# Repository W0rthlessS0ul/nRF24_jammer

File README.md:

<div align="center">
  
  <h1> 🌟 nRF24 Jammer 🌟 </h1>
</div>

Welcome to the **nRF24 Jammer** repository! 🎉 Dive into the world of RF interference with this unique project based on the ESP32 and nRF24 technology.

## 📚 Table of Contents
- [🚀 What Can You Do with This?](#-what-can-you-do-with-this)
- [📱 Ported Firmware](#-ported-firmware)
- [📟 Supported & Community PCBs](#-supported-&-community-pcbs)
- [📋 List of Components](#-list-of-components)
- [🧑‍🔧 Let's Get Started with Soldering!](#-lets-get-started-with-soldering)
- [🛠️ Build From Source](#-build-from-source)
- [📦 Flash Firmware](#-flash-firmware)
- [🎮 Device Control](#-device-control)
- [🌐 Web Interface](#-Web-Interface)
- [🔌 Serial Interface](#-Serial-Interface)
- [🎉 Final Outcome](#-final-outcome)
- [🙏 Acknowledgments](#-acknowledgments)
- [🤝 Project Supporters](#-project-supporters)
- [❤️ Support the project](#-support-the-project)
- [⭐ Star History](#-star-history)

-----

## 🚀 What Can You Do with This?
This amazing jammer is built on the **ESP32** architecture integrated with **configurable numbers of nRF24** modules. With its extraordinary capabilities, you can effectively disrupt signals across different technologies including:
- **Bluetooth** 🔊
- **BLE** 📱
- **Drones** 🚁
- **Wi-Fi** 📶
- **Zigbee**📡

-----

## 📱 Ported Firmware

| Device       | Repository URL                                                      |
|--------------|---------------------------------------------------------------------|
| Flipper Zero | [FZ_nRF24_jammer](https://github.com/W0rthlessS0ul/FZ_nRF24_jammer) |
| LOLIN32 Lite | [nRF24_jammer](https://github.com/gitati16/nRF24_jammer)            |

-----

## 📋 List of Components
To bring this project to life, you will need the following components:

1. <details><summary><b>nRF24 modules 🛠️</b></summary>

    *Any nRF24 modules are suitable, but **CDEBYTE E01-2G4M27D** is recommended*

   </details>

2. **ESP-WROOM-32** ⚙️
3. **16V capacitors** rated at **100µF** 🔋
4. **128x32 or 128x64 OLED display** 📺 *(optional)*
5. **Tactile button** 🔘 *(optional)*

-----

## 📟 Supported & Community PCBs

| Preview | Author | Rev | Board README |
|---------|--------|-----|--------------|
|  | [@W0rthlessS0ul](https://github.com/W0rthlessS0ul) | `v1.0.0` | [README](/PCB/W0rthlessS0ul/v1.0.0/README.md) |

> 💡 **Want to contribute your own PCB design?**  
> If you feel confident in designing a high-quality PCB, feel free to submit your board via a **Pull Request**!  
> 
> - **Well-engineered and verified designs** will be merged directly into the repository.  
> - If there are any doubts regarding layout quality, routing, or component selection, a thread will be opened in **[Discussions](https://github.com/W0rthlessS0ul/nRF24_jammer/discussions)** so the community can review, discuss, and vote on whether it should be added.

-----

## 🧑‍🔧 Let's Get Started with Soldering!

### Connecting First nRF24 module (**optional**)
| **Pin Name** | **ESP32 GPIO** | **Connection**       |
|--------------|----------------|----------------------|
| VCC          | 3.3V          | (+) capacitor        |
| GND          | GND           | (-) capacitor        |
| CE           | GPIO 16       |                      |
| CSN          | GPIO 15       |                      |
| SCK          | GPIO 14       |                      |
| MOSI         | GPIO 13       |                      |
| MISO         | GPIO 12       |                      |
| IRQ          |                |                      |

### Connecting Second nRF24 module (**optional**)
| **Pin Name** | **ESP32 GPIO** | **Connection**       |
|--------------|----------------|----------------------|
| VCC          | 3.3V          | (+) capacitor        |
| GND          | GND           | (-) capacitor        |
| CE           | GPIO 18       |                      |
| CSN          | GPIO 17       |                      |
| SCK          | GPIO 14       |                      |
| MOSI         | GPIO 13       |                      |
| MISO         | GPIO 12       |                      |
| IRQ          |                |                      |

### Connecting Third nRF24 module (**optional**)
| **Pin Name** | **ESP32 GPIO** | **Connection**       |
|--------------|----------------|----------------------|
| VCC          | 3.3V          | (+) capacitor        |
| GND          | GND           | (-) capacitor        |
| CE           | GPIO 23       |                      |
| CSN          | GPIO 19       |                      |
| SCK          | GPIO 14       |                      |
| MOSI         | GPIO 13       |                      |
| MISO         | GPIO 12       |                      |
| IRQ          |                |                      |

### Connecting Fourth nRF24 module (**optional**)
| **Pin Name** | **ESP32 GPIO** | **Connection**       |
|--------------|----------------|----------------------|
| VCC          | 3.3V          | (+) capacitor        |
| GND          | GND           | (-) capacitor        |
| CE           | GPIO 5        |                      |
| CSN          | GPIO 4        |                      |
| SCK          | GPIO 14       |                      |
| MOSI         | GPIO 13       |                      |
| MISO         | GPIO 12       |                      |
| IRQ          |                |                      |

### Connecting Fifth nRF24 module (**optional**)
| **Pin Name** | **ESP32 GPIO** | **Connection**       |
|--------------|----------------|----------------------|
| VCC          | 3.3V          | (+) capacitor        |
| GND          | GND           | (-) capacitor        |
| CE           | GPIO 33       |                      |
| CSN          | GPIO 32       |                      |
| SCK          | GPIO 14       |                      |
| MOSI         | GPIO 13       |                      |
| MISO         | GPIO 12       |                      |
| IRQ          |                |                      |

### OLED Connection (**optional**)
| **Pin Name** | **ESP32 GPIO** |
|--------------|----------------|
| VCC          | 3.3V          |
| GND          | GND           |
| SCL          | GPIO 22       |
| SDA          | GPIO 21       |

### Button Connection (**optional**)
| **Button Actions** | **ESP32 GPIO** |
|--------------|----------------|
| OK          | GPIO 25       |
| NEXT (Optional)             | GPIO 26       |
| PREVIOUS (Optional)            | GPIO 27       |

###### In all configurations the same SCK, MOSI, and MISO pins are used. This is not a mistake - SPI interfaces can share clock and data lines, while proper operation is ensured by separate control signals (CSN and CE)

-----

## 🛠️ Build From Source

#### `This section is addressed to contributors. If you are a regular user of the project, you can skip it`

1. Install **PlatformIO IDE** extension in **VS Code** 
2. Click the PlatformIO icon → Open → Open Project → select your project folder
3. Wait until all dependencies are installed
4. And now you can choose which project to compile in "PROJECT TASKS" or choose "Build all" to compile all kinds of firmware at once.
5. Output .bin files appear in: ```project_root/bin/[env_name]```

###### ⚠️ Important for source builds: Since v2.5.0, this project uses a modified RF24 library (see /lib).

-----

## 📦 Flash Firmware
<details>
<summary><strong>Manual Update</strong></summary>

<div style="margin-left: 20px;">

Follow these steps to flash the firmware:
1. Download the firmware from the **[releases](https://github.com/W0rthlessS0ul/nRF24_jammer/releases)** section that corresponds to your display
2. Navigate to **ESPWebTool**: [ESPWebTool](https://esp.huhn.me/)
3. Arrange the files as per the table below:

| **Address** | **File Name**                             |
|-------------|-------------------------------------------|
| 0x1000      | bootloader.bin              |
| 0x8000      | partitions.bin              |
| 0x10000     | firmware.bin                          |

4. Click "Flash," and once the installation is complete, **restart your board** and enjoy using your jammer!

</div>
</details>
<details>
<summary><strong>OTA Update</strong></summary>

<div style="margin-left: 20px;">

### This method can only be used if you have firmware version 1.9 or higher installed.
Follow these steps to flash the firmware:
1. Download the firmware from the **[releases](https://github.com/W0rthlessS0ul/nRF24_jammer/releases)** section that corresponds to your display
2. Turn on your device and open a web browser
3. Navigate to the web interface at **192.168.4.1**
4. Click on "**OTA**" and select the file "**firmware.bin**" (`⚠️️ make sure not to choose the bootloader or partitions files`)

</div>
</details>

-----

## 🎮 Device Control 

<details>
<summary><strong>🟢 1-Button Configuration</strong></summary>
<div style="margin-left: 20px;">

#### 📋 Menu Navigation
- **Short press** → Next menu item
- **Long press** → Select menu item

#### 📡 Misc Jammer
- **Short press** → Channel +1
- **Long press** → Continuous channel +1 (every 100ms)
- **Double press** → Select channel

#### 📡 WiFi Attack
- **Short press** → Stop attack
- **Double press** → Switch between jam\deauth

</div>
</details>

<details>
<summary><strong>🔵 2-Button Configuration</strong></summary>
<div style="margin-left: 20px;">

#### 📋 Menu Navigation
- **Next button** short press → Next menu item
- **OK button** short press → Select menu item

#### 📡 Misc Jammer
- **Next button** short press → Channel +1
- **Next button** long press → Continuous channel +1 (every 100ms)
- **OK button** short press → Select channel

#### 📡 WiFi Attack
- **Short press** → Stop attack
- **Next button** → Switch between jam\deauth

</div>
</details>

<details>
<summary><strong>🟣 3-Button Configuration</strong></summary>
<div style="margin-left: 20px;">

#### 📋 Menu Navigation
- **Next button** short press → Next menu item
- **Previous button** short press → Previous menu item
- **OK button** short press → Select menu item

#### 📡 Misc Jammer
- **Next button** short press → Channel +1
- **Next button** long press → Continuous channel +1 (every 100ms)
- **Previous button** short press → Channel -1
- **Previous button** long press → Continuous channel -1 (every 100ms)
- **OK button** short press → Select channel

#### 📡 WiFi Attack
- **Short press** → Stop attack
- **Next button** → Switch between jam\deauth
- **Previous button** → Switch between jam\deauth

</div>
</details>

-----

## 🌐 Web Interface

- To utilize the web interface, please follow the steps outlined below
1. activate the **nRF24 jammer**
2. Connect to the Wi-Fi network named `jammer` using the password `W0rthlessS0ul`
3. open your web browser and navigate to the IP address `192.168.4.1`
4. Now you can control your nRF24 jammer through an web interface

-----

## 🔌 Serial Interface

- To utilize the serial interface, please follow the steps outlined below
1. Activate the **nRF24 jammer**
2. Connect the device to a PC or phone via USB
3. You can use any serial terminals for control, for example: [spacehuhn terminal](https://terminal.spacehuhn.com/)
4. Now write **help** to get a list of commands

-----

## 🎉 Final Outcome

### Normal Spectrum

### Bluetooth Jam Spectrum

### Drone Jam Spectrum

### Wi-Fi Jam Spectrum

### BLE Jam Spectrum

### Zigbee Jam Spectrum

### Misc Jam Spectrum

-----

## 🙏 Acknowledgments
- [smoochiee](https://github.com/smoochiee) - **for the main logic of the jammer.**
- [samukas81](https://github.com/samukas81) - **for suggesting ideas.**

-----

## 🤝 Project Supporters

| **Supporter**                                  | **Contribution**|
|------------------------------------------------|-----------------|
|  [@sergey2735](https://github.com/sergey2735)  |    40.7 ADA     |

-----

## ❤️ Support the Project

If you find this project useful and want to support its ongoing development, consider starring the repository ⭐, following the author, or buying a cup of coffee to keep things fueled! ☕

<div align="center">
  <table width="70%">
    <tr>
      <td width="50%" align="center">
        
      </td>
      <td width="50%" align="center">
        
      </td>
    </tr>
  </table>
</div>

<br>

<details>
<summary><b>🪙 Direct Cryptocurrency Transfer</b></summary>
<br>

| Coin / Network | Direct Wallet Address |
| :--- | :--- |
| 🟧 **Bitcoin (BTC)** | `bc1qvul4mlxxw5h2hnt8knnxdrxuwgpf4styyk20tm` |
| 🔷 **Ethereum (ETH)** | `0x5c54eAb2acFE1c6C866FB4b050d8B69CfB1138Af` |
| ⚪ **Litecoin (LTC)** | `LbdzCsYbxuD341raar6Cg1yKavaDq7fjuV` |
| ⚫ **Ripple (XRP)** | `rKLLPzoBGfqY3pAQPwTFPRYaWjpHSwHNDw` |
| 🔵 **Cardano (ADA)** | `addr1qyz2aku0ucmxqnl60lza23lkx2xha8zmxz9wqxnrtvpjysgy4mdcle3kvp8l5l7964rlvv5d06w9kvy2uqdxxkcryfqs7pajev` |
| 🟡 **Dogecoin (DOGE)** | `DBzAvD62yQUkP4Cb7C5LuFYQEierF3D3oG` |

</details>

<br>

> Every donation is greatly appreciated and directly contributes to the development, testing, and new hardware revisions of this project!

---

## ⭐ Star History

<a href="https://star-history.dera.page/#W0rthlessS0ul/nRF24_jammer&type=date&legend=top-left">
 <picture>
   <source media="(prefers-color-scheme: dark)" srcset="https://star-history.dera.page/svg?repos=W0rthlessS0ul/nRF24_jammer&type=date&theme=dark&legend=top-left" />
   <source media="(prefers-color-scheme: light)" srcset="https://star-history.dera.page/svg?repos=W0rthlessS0ul/nRF24_jammer&type=date&legend=top-left" />
   
 </picture>
</a>

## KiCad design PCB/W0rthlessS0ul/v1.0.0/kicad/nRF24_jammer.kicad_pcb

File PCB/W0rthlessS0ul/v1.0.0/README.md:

<div align="center">

[⬅️ Back to Main Repository](/README.md)

# 📟 nRF24 Jammer Board (v1.0.0)

### Designed by [@W0rthlessS0ul](https://github.com/W0rthlessS0ul)

</div>

-----

## 📋 Board Specifications
* **MCU:** ESP-WROOM-32D
* **USB-to-UART:** CP2104
* **RF Modules:** One CDEBYTE E01-2G4M27D module
* **Display:** OLED 128x64
* **Controls:** 3 navigation buttons
* **Power Source:** 3.7V Li-Po battery with onboard Type-C charging circuit

-----

## ⚠️ Known Issues & Hardware Limitations

> **Please review the following hardware quirks of revision v1.0.0 before ordering and assembling:**

1. **Connected Battery Required (No Power Path):**  
   The board **cannot operate exclusively via USB Type-C without a battery connected**. It lacks a dedicated dynamic power-path management circuit. Without a battery, current is drawn directly through the onboard charging controller, which is capped at ~500mA. This is insufficient to handle simultaneous ESP32 transmission peaks and CDEBYTE module transmitting at full power, causing brownouts and bootloops
   
   👉 **A connected battery is strictly required for normal operation**
2. **Charging Status LED:**  
   In some instances, the charge status LED may remain dimly lit or fail to turn off completely even after the battery reaches full charge

-----

## 🖨️ 3D Enclosure

> **If you plan to use the 3D enclosure:**

- The case is specifically modeled for a **603450** Li-Po cell

-----

## 📸 Gallery

<div align="center">
  <table>
    <tr>
      <td align="center"><b>PCB Front</b></td>
      <td align="center"><b>PCB Back</b></td>
    </tr>
    <tr>
      <td></td>
      <td></td>
    </tr>
    <tr>
      <td align="center"><b>3D Case (Solid)</b></td>
      <td align="center"><b>3D Case (X-Ray)</b></td>
    </tr>
    <tr>
      <td></td>
      <td></td>
    </tr>
  </table>
</div>

-----

## 📦 Files

| Resource | Description | Link |
| :--- | :--- | :---: |
| 🗜️ **Gerber Files** | Production-ready archive | [Download ZIP](gerber/nRF24_jammer.zip) |
| 📝 **BOM** | Bill of Materials | [View BOM](BOM/nRF24_jammer.csv) |
| 📐 **Schematic** | Electrical schematic | [Download PDF](/schemes/W0rthlessS0ul/v1.0.0/nRF24_jammer.pdf) |
| 🛠️ **KiCad Project** | Full project files | [Open Directory](kicad/) |
| 🖨️ **3D Enclosure** | Printable case models | [Open Directory](enclosure/) |

-----

## 📐 Electrical Schematic

<div align="center">

  <td></td>

</div>

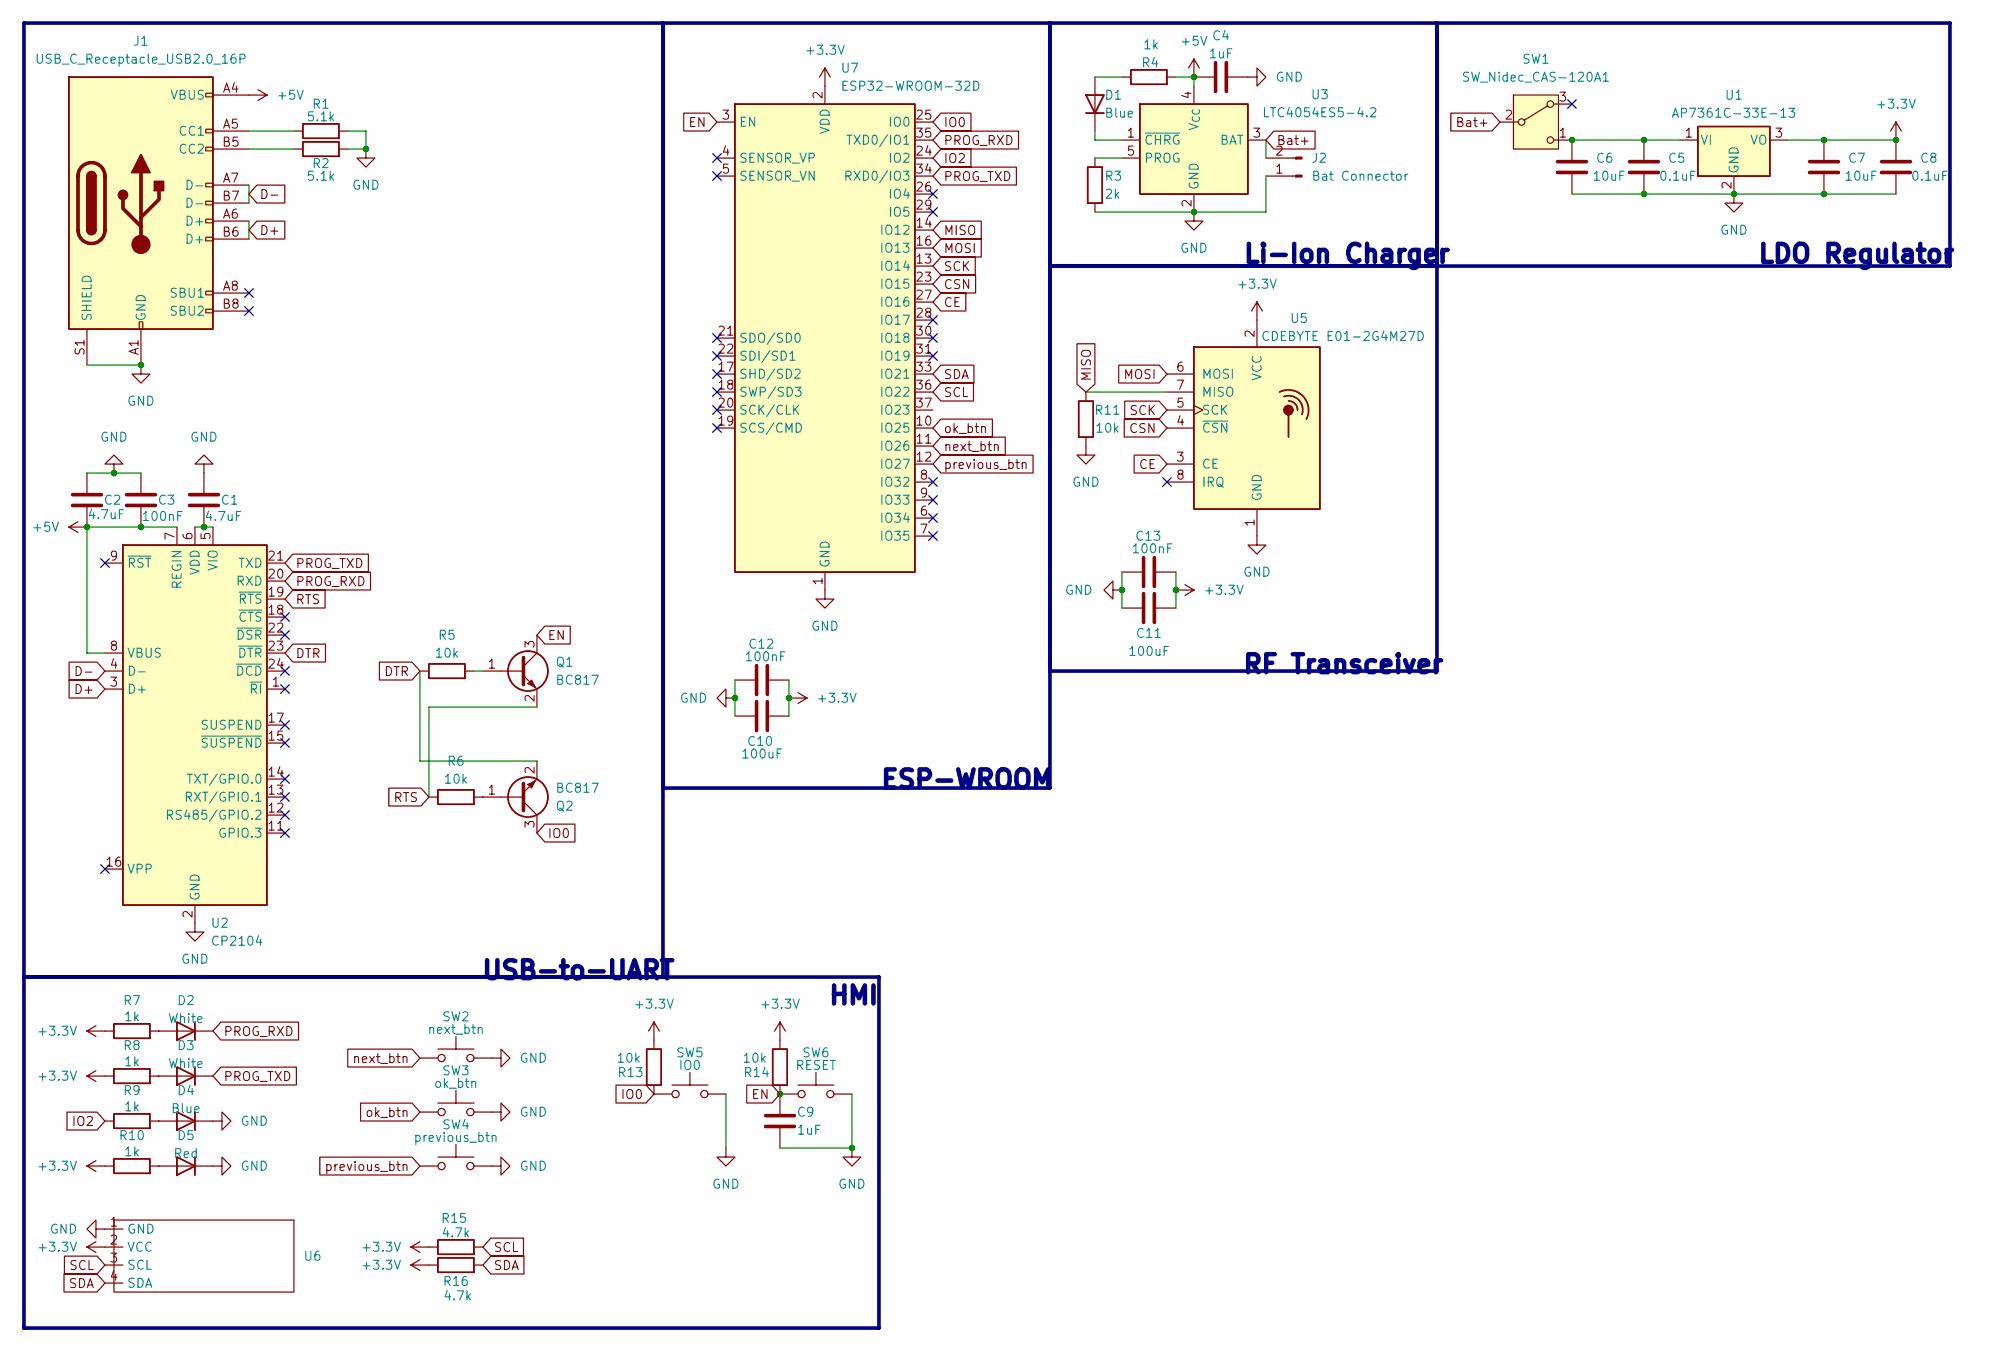
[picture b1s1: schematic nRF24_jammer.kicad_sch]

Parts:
C1, C2: 4.7uF; C_0603_1608Metric
C3, C12, C13: 100nF; C_0402_1005Metric
C4, C9: 1uF; C_0402_1005Metric
C5, C8: 0.1uF; C_0402_1005Metric
C6, C7: 10uF; C_0805_2012Metric
C10, C11: 100uF; C_1210_3225Metric
D1, D4: Blue; D_0402_1005Metric
D2, D3: White; D_0402_1005Metric
D5: Red; D_0402_1005Metric
J1: USB_C_Receptacle_USB2.0_16P; USB_C_Receptacle_HCTL_HC-TYPE-C-16P-01A
J2: Bat Connector; PinHeader_1x02_P2.54mm_Vertical
Q1, Q2: BC817; SOT-23
R1, R2: 5.1k; R_0402_1005Metric
R3: 2k; R_0402_1005Metric
R4, R7, R8, R9, R10: 1k; R_0402_1005Metric
R5, R6, R11, R13, R14: 10k; R_0402_1005Metric
R15, R16: 4.7k; R_0402_1005Metric
SW1: SW_Nidec_CAS-120A1; SW_Slide_SPDT_Angled_CK_OS102011MA1Q
SW2: next_btn; SW_Push_1TS009xxxx-xxxx-xxxx_6x6x5mm
SW3: ok_btn; SW_Push_1TS009xxxx-xxxx-xxxx_6x6x5mm
SW4: previous_btn; SW_Push_1TS009xxxx-xxxx-xxxx_6x6x5mm
SW5: IO0; SW_Push_1P1T-MP_NO_Horizontal_Alps_SKRTLAE010
SW6: RESET; SW_Push_1P1T-MP_NO_Horizontal_Alps_SKRTLAE010
U1: AP7361C-33E-13; SOT-223-3_TabPin2
U2: CP2104; QFN-24-1EP_4x4mm_P0.5mm_EP2.6x2.6mm
U3: LTC4054ES5-4.2; TSOT-23-5
U5: CDEBYTE E01-2G4M27D; E01-2G4M27D
U6: Display 0.96 breakout board
U7: ESP32-WROOM-32D

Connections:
+3.3V: C7.1, C8.1, C10.2, C11.1, C12.2, C13.2, R7.1, R8.1, R10.1, R13.1, R14.1, R15.1, R16.1, U1.3 (VO), U5.2 (VCC), U6.2 (VCC), U7.2 (VDD)
+5V: C2.2, C3.2, C4.1, J1.A4 (VBUS), J1.A9 (VBUS), J1.B4 (VBUS), J1.B9 (VBUS), R4.2, U2.7 (REGIN), U2.8 (VBUS), U3.4 (V_{CC})
Bat+: J2.2, SW1.2 (B), U3.3 (BAT)
CE: U5.3 (CE), U7.27 (IO16)
CSN: U5.4 (~CSN), U7.23 (IO15)
D+: J1.A6 (D+), J1.B6 (D+), U2.3 (D+)
D-: J1.A7 (D-), J1.B7 (D-), U2.4 (D-)
DTR: Q2.2 (E), R5.1, U2.23 (~DTR)
EN: C9.1, Q1.3 (C), R14.2, SW6.1, U7.3 (EN)
GND: C1.1, C2.1, C3.1, C4.2, C5.2, C6.2, C7.2, C8.2, C9.2, C10.1, C11.2, C12.1, C13.1, D4.1 (K), D5.1 (K), J1.A1 (GND), J1.A12 (GND), J1.B1 (GND), J1.B12 (GND), J1.S1 (SHIELD), J2.1, R1.2, R2.2, R3.2, R11.2, SW2.2, SW3.2, SW4.2, SW5.2, SW6.2, U1.2 (GND), U2.2 (GND), U2.25 (GND), U3.2 (GND), U5.1 (GND), U6.1 (GND), U7.1 (GND), U7.15 (GND), U7.38 (GND), U7.39 (GND)
IO0: Q2.3 (C), R13.2, SW5.1, U7.25 (IO0)
IO2: R9.1, U7.24 (IO2)
MISO: R11.1, U5.7 (MISO), U7.14 (IO12)
MOSI: U5.6 (MOSI), U7.16 (IO13)
unnamed: D1.2 (A), R4.1
unnamed: D1.1 (K), U3.1 (~CHRG)
unnamed: D2.2 (A), R7.2
unnamed: D3.2 (A), R8.2
unnamed: D4.2 (A), R9.2
unnamed: D5.2 (A), R10.2
unnamed: J1.A5 (CC1), R1.1
unnamed: J1.B5 (CC2), R2.1
unnamed: Q1.1 (B), R5.2
unnamed: Q2.1 (B), R6.2
unnamed: C5.1, C6.1, SW1.1 (C), U1.1 (VI)
unnamed: C1.2, U2.5 (VIO), U2.6 (VDD)
unnamed: R3.1, U3.5 (PROG)
PROG_RXD: D2.1 (K), U2.20 (RXD), U7.35 (TXD0/IO1)
PROG_TXD: D3.1 (K), U2.21 (TXD), U7.34 (RXD0/IO3)
RTS: Q1.2 (E), R6.1, U2.19 (~RTS)
SCK: U5.5 (SCK), U7.13 (IO14)
SCL: R15.2, U6.3 (SCL), U7.36 (IO22)
SDA: R16.2, U6.4 (SDA), U7.33 (IO21)
next_btn: SW2.1, U7.11 (IO26)
ok_btn: SW3.1, U7.10 (IO25)
previous_btn: SW4.1, U7.12 (IO27)

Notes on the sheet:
RF Transceiver
ESP-WROOM
HMI
USB-to-UART
Li-Ion Charger
LDO Regulator

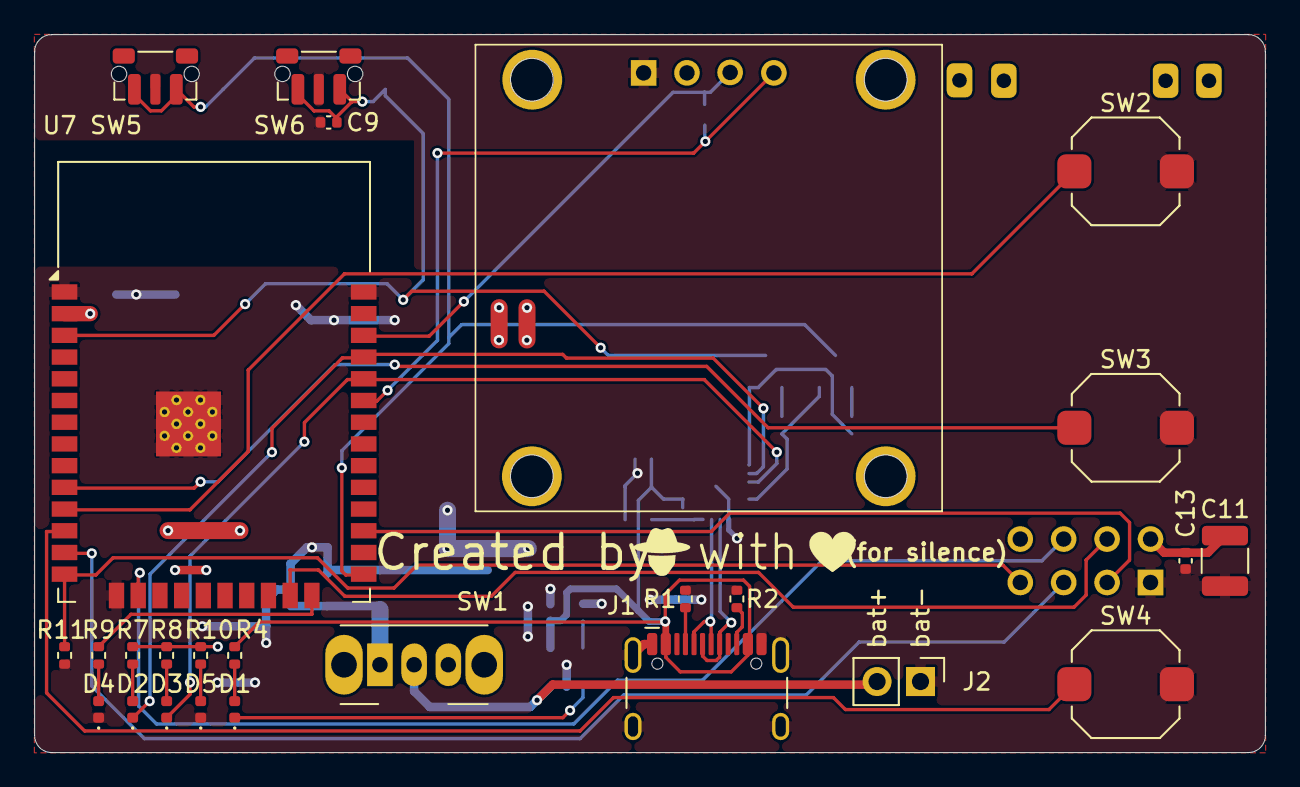
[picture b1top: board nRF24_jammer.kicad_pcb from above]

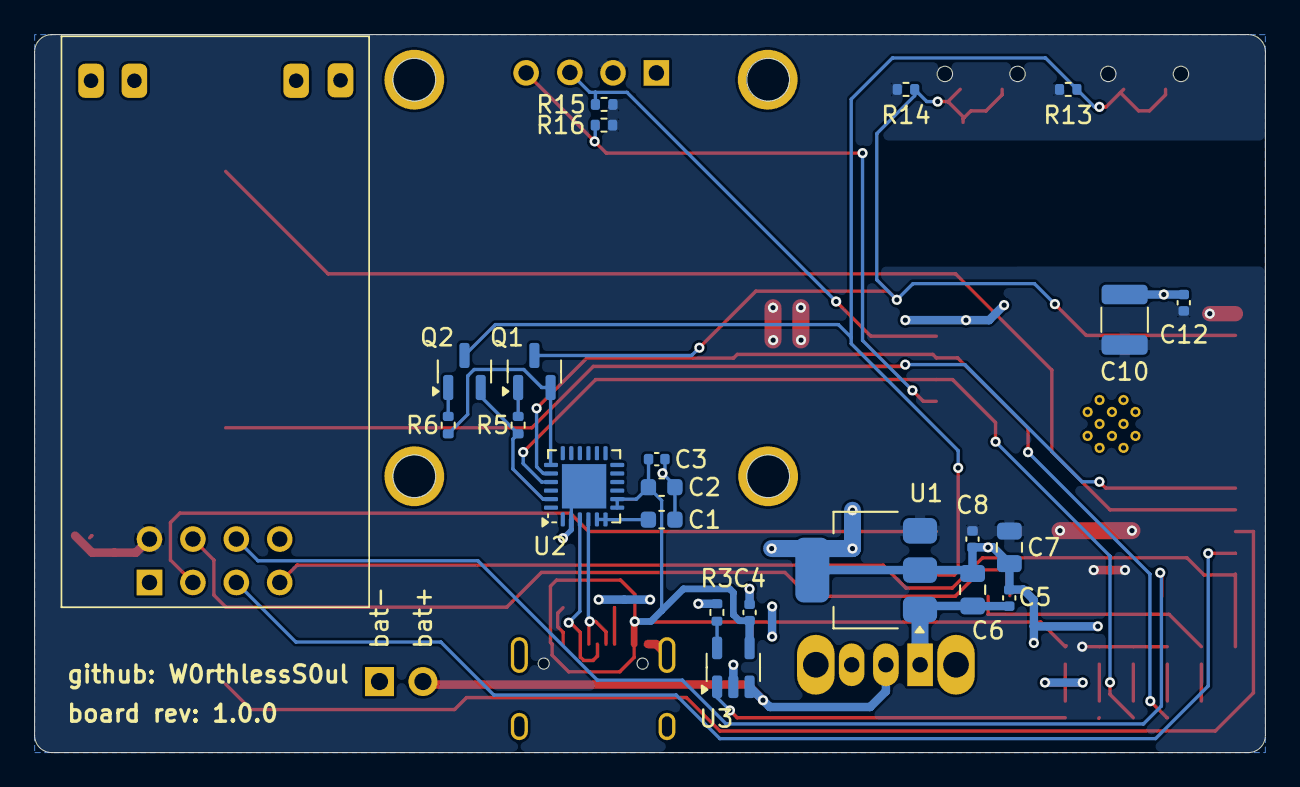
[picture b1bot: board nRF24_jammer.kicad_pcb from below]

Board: 2 copper layers, 72.0 x 42.0 mm, 49 parts (23 on the bottom side), 36 nets.

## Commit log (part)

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2024-09-13 new bitmap
2024-09-13 Web interface added
    Web interface added
2024-09-15 new web_interface.jpg
2024-09-15 added new web interface
2024-09-16 The principles of suppression have been revised. Bluetooth and BLE are now categorized separately.
    The principles of suppression have been revised. Bluetooth and BLE are now categorized separately.
2024-09-17 Some graphic changes.
    The photos for the Bluetooth Jam spectrum have been updated, and additional photos for the BLE Jam spectrum have been added.
2024-09-19 some changes
2024-09-25 new web_interface.jpg
    new web_nterface.jpg
2024-10-15 The updated firmware version.
    1. An error in the web interface has been fixed.
    2. The Wi-Fi password has been changed from W0rthlesS0ul to W0rthlessS0ul.
    3. Bitmap images have been redesigned.
    4. A jammer for the Zigbee protocol has been implemented (all frequency data was sourced from the internet, and I do not have Zigbee devices for validation).
    5. Control for the Zigbee jammer has been added via bitmap interface and web interface.
    6. The README.md file has been updated with new descriptions and information.
2024-10-27 Support for 128x64 displays has been added.
    Support for 128x64 displays has been added.
2024-11-15 Support for devices without a display has been added.
    Support for devices without a display has been added.
2024-11-20 New Improvements
    A new feature has been added: the Misc Jammer, which allows users to jam specified channels.
    A feature to disable the logo during startup has also been added.
2024-11-23 refactor
2024-11-24 Code improvements that do not impact performance.
    The code has become shorter and more readable. Special thanks to 9dl.
2024-11-24 The error caused by my inattention has been corrected.
2024-11-24 The ability for OTA (Over-The-Air) updates has been added.
    The ability for OTA (Over-The-Air) updates has been added.
2024-12-09 New Improvements
    1. The logo in the web interface has been updated for a better appearance.
    2. A new feature has been added based on the idea from this issue: https://github.com/W0rthlessS0ul/nRF24_jammer/issues/9. Special thanks to samukas81 for the suggestion.
2024-12-14 New Improvements
    1. Improved web interface.
    2. The error with the OTA update has been fixed.
    3. The option to disable the access point has been added. (Thanks to samukas81 for the idea.)
2025-02-06 New Improvements
    The option to use one, two, or three buttons for control has been added. (Thanks to [shuixing1122](https://github.com/shuixing1122) for the idea.)
    - A Compact version has been added
    - The standard version with two nRF24 is now called Standard
2025-02-08 New Improvements
    Added the ability to exit the jamming mode by pressing the OK button (25 pin).
2025-02-21 Gifs added
    Some of the JPEGs have been replaced with GIFs
2025-04-25 Added the ability to change the ssid and password of the wifi network
    1. Added the ability to change the ssid and password of the wifi network
2025-05-01 Update README.md
    inaccuracy fixed (thanks [zelamuss](https://github.com/zelamuss))
2025-05-20 Added synchronization of the web server with the screen
    Added synchronization of the web server with the screen
2025-05-21 new version
    The library is now modified + bug fixed in "compact" versions
2025-05-21 slightly changed readme.md
    slightly changed readme.md
2025-05-21 New GIFs for WiFi and Zigbee
2025-05-21 fixed a bug with a broken ble jammer
    fixed a bug with a broken ble jammer
2025-05-31 Add full ble and bluetooth
2025-06-01 Here's the updated commit message:
    Add serial command control to nRF24_jammer (without OLED)
    This commit introduces serial command functionality to the nRF24_jammer project, allowing you to control and configure the jammer via a serial interface.
    Key changes:
    - **Serial Command Parsing**: I implemented logic in `nRF24_jammer.ino` to read, parse, and execute commands received over the serial port (baud rate 115200).
    - **Jamming Control**: I added commands to start and stop various jamming modes (Bluetooth, Wi-Fi, Drone, BLE, Zigbee, Misc).
    - **Configuration**: I added commands to set jamming parameters such as Bluetooth/Drone/Misc methods, Wi-Fi channel, and module operation mode (se
2025-06-02 new version
    1. Increased button hold delay to up to 600 ms for better press detection (Thanks to [McVillano](https://github.com/McVillano) for the idea)
    2. Reduced the delay for click buttons, making the interface more responsive
    3. Fixed a bug that prevents attacks from resuming after being stopped (Thanks to [samukas81](https://github.com/samukas81) for detecting the error)
2025-06-16 Create LICENSE
2025-07-05 new version (2.5.2)
    1. Fixed a bug that could cause the jammer to not work on all channels or not work at all
    2. Refactored code structure: moved function implementations from headers (*.h) to *.cpp files, keeping only declarations in headers
    3. All used libraries have been added to the /lib folder
2025-07-21 added schemas
2025-08-29 new version (2.6.0)
    Added a new firmware version called "Flexible"
2025-11-10 new version (2.7.0)
    1. Added control via the serial interface
    2. Added modules deinitialization after the attack is completed
2025-11-21 new version (2.8.0)
    1. Added firmware version display on the OTA update page
    2. Added the ability to configure nRF24 pins via the Serial interface
    3. The Serial interface now outputs 'ok' after sending a response
    4. The Serial 'info' command now includes the firmware version number, firmware type, and screen size
    5. Added the ability to disable the display via the Web and Serial interfaces
    6. The Web and Serial interfaces now display the current value of settings
2025-11-21 new version (2.8.0)
2026-01-05 Remove obsolete editions
2026-01-08 new version (2.9.0)
    Added the ability to send commands for the Serial interface using GET requests
    Added the ability to configure the power amplifier level
    Web interface has been improved
    Fixed a bug in misc jammer
    A Serial terminal has been added to the Web interface
    Fixed a bug in zigbee jammer (thanks yashikada)
2026-01-08 new version (2.9.0)
    One more fixed a bug in zigbee jammer (thanks yashikada)
2026-01-08 new version (2.9.0)
    One more fix
2026-01-08 new gifs
2026-01-11 Migrates to proper platformio setup
2026-01-12 Revise README for OTG Jammer project
    Updated README to reflect project fork and new features.
2026-01-12 Update Adafruit libs
2026-01-12 Remove UART console, webpage and unused libs
2026-01-12 Remove old project files
2026-01-12 Update license
2026-01-26 Added Project Supporters section
2026-02-07 new version (3.0.0)
    - Bug fixed in misc jammer
    - The PA setting has been added to serial settings
    - Web interface adapted for mobile devices
    - Captive portal added – redirects to control panel on connect
    - Fixed a flaw in wifi select
    - Added APs count per WiFi channel in WiFi Select
2026-02-08 Added the Build From Source section
2026-02-08 Added star history
2026-02-13 new version (3.0.1)
    Correcting dumb mistakes
2026-02-25 new version (3.1.0)
    Added SSID display in WiFi Select Channel (idea ElberTavares)
    Completely redesigned control via Serial
    The scan sub-item has been added to Serial
    Added separation of BLE into Advertising Channels and Data Channels
    Replaced GET requests with POST/redirect for settings updates
    WiFi All added support for 14 channels
2026-03-06 Added a donation button
2026-04-20 new version (3.2.0)
    - Added Deauth attack (Thanks ElberTavares)
    - Added BLE scanner to serial
    - Added a settings file for clang-format
    - Fixed a bug in WiFi channel jam
    - The attack sub-item has been added to Serial
2026-05-03 different random channels in separate mode
2026-06-02 feat: port to ESP32 WeMos LOLIN32 Lite + nRF24L01+PA+LNA
    - Add include/128x64_LOLIN32/ with adapted config.h
    * VSPI instead of HSPI (GPIO 18/19/23)
    * CE=GPIO4, CSN=GPIO5
    * LED_PIN=GPIO22 (active LOW)
    * BTN_OK=GPIO34, BTN_NEXT=GPIO35 (INPUT-ONLY, external pull-up required)
    * BTN_PREV=GPIO32
2026-06-02 feat: port to ESP32 WeMos LOLIN32 Lite + nRF24L01+PA+LNA
    - board: lolin32_lite (VSPI, LED GPIO22 active-LOW)
    - config.h: pin CE=4 CSN=5 SCK=18 MOSI=23 MISO=19
    - buttons: GPIO34/35 (INPUT-ONLY, ext pull-up) + GPIO32
    - Wire.begin(21,22) explicit for I2C
    - jam.cpp: HSPI→VSPI, 10MHz SPI, LED active-LOW
    - nRF24_jammer.cpp: LED GPIO22 active-LOW, Wire.begin
2026-06-02 fix: add missing source files for LOLIN32 (setup/loop/bitmap/html)
2026-06-13 Hardened AP startup before DNS
    Added explicit AP mode initialization and short settle delay before SoftAP start. This prevents possible bootloops.
2026-06-13 Added EEPROM-empty SSID fallback and debug log
2026-06-13 Update .gitignore to include bin output folder
2026-06-16 new version (3.3.0)
    Added WiFi Beacon Spam (Thanks ElberTavares)
    Switching from EEPROM library to Preferences
    Added separation of tasks by cores, during jamming
    Fixed a bug in random jamming methods (Thanks reimerp)
    Fixed a bug with duplicate random values
    Fixed bug with non-disconnecting AP (Thanks Suyu-san for finding bug)
2026-06-21 new version (3.3.0)
    - Added WiFi Beacon Spam (Thanks ElberTavares)
    - Switching from EEPROM library to Preferences
    - Added separation of tasks by cores, during jamming
    - Fixed a bug in random jamming methods (Thanks reimerp)
    - Fixed a bug with duplicate random values
    - Fixed bug with non-disconnecting AP (Thanks Suyu-san for finding bug)
